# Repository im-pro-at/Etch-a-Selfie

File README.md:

# Etch-a-Selfie
ESP32_CAM meets Etch-A-Sketch => Etch-a-Selfie

## System Overview

## Software

The Software uses [GRBL](https://github.com/bdring/Grbl_Esp32) to controll the stepper motors.

A test implementation in JavaScript of the algorithms used is available [here](https://etch-a-selfie.im-pro.at/).

[Used Libraries](Sketch/ReadMe.md)

## BOM

[here](PCB/BOM.md)

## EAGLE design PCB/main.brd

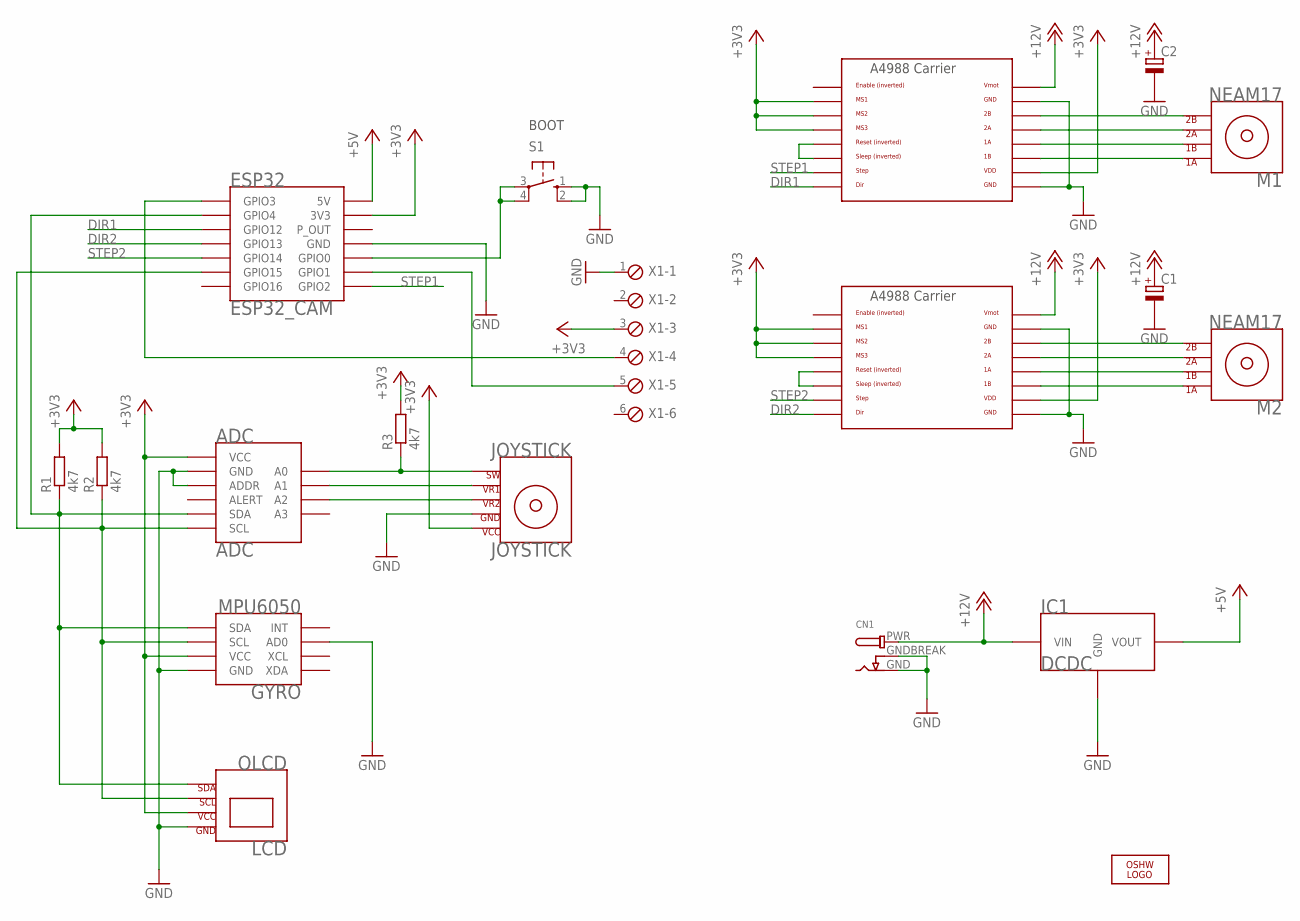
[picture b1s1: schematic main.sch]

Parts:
ADC: ADC
C1, C2: CPOL-EUE2.5-6; E2,5-6
CN1: DCBARRELPTH; DCJACK_2MM_PTH
ESP32: ESP32_CAM
GYRO: MPU6050
IC1: DCDC
IC2, IC3: A4988BREAKOUT
JOYSTICK: JOYSTICK
LCD: OLCD
LOGO1: OHW-LOGO_OSHW_LOGO_FILLX0350-NT; OHW-LOGO_OSHW_FILLX350_NOTEXT
M1, M2: NEAM17; NEMA17
R1, R2, R3: 4k7; 0207/10
S1: 10-XX; B3F-10XX
X1: MPT6; 6POL254

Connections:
+3V3: ADC.VCC, ESP32.3V3, GYRO.VCC, IC2.MS1, IC2.MS2, IC2.MS3, IC2.VDD, IC3.MS1, IC3.MS2, IC3.MS3, IC3.VDD, JOYSTICK.VCC, LCD.VCC, R1.2, R2.2, R3.2, X1.3
+5V: ESP32.5V, IC1.VOUT
+12V: C1.+, C2.+, CN1.PWR, IC1.VIN, IC2.VMOT, IC3.VMOT
DIR1: ESP32.GPIO12, IC2.DIR
DIR2: ESP32.GPIO13, IC3.DIR
GND: ADC.ADDR, ADC.GND, C1.-, C2.-, CN1.GND, CN1.GNDBREAK, ESP32.GND1 (GND), ESP32.GND2 (GND), ESP32.GND3 (GND), GYRO.AD0, GYRO.GND, IC1.GND1 (GND), IC1.GND2 (GND), IC2.GND, IC2.GND@0 (GND), IC3.GND, IC3.GND@0 (GND), JOYSTICK.GND, LCD.GND, S1.1 (S), S1.2 (S1), X1.1
unnamed: IC2.1B, M1.1A
unnamed: IC2.RST, IC2.SLP (SLEEP)
unnamed: IC2.2B, M1.2B
unnamed: IC2.2A, M1.2A
unnamed: IC2.1A, M1.1B
unnamed: IC3.RST, IC3.SLP (SLEEP)
unnamed: IC3.2B, M2.2B
unnamed: IC3.2A, M2.2A
unnamed: IC3.1A, M2.1B
unnamed: IC3.1B, M2.1A
unnamed: ESP32.GPIO1, X1.5
unnamed: ESP32.GPIO3, X1.4
unnamed: ESP32.GPIO0, S1.3, S1.4 (P1)
unnamed: ADC.A0, JOYSTICK.SW, R3.1
unnamed: ADC.A1, JOYSTICK.VR1
unnamed: ADC.A2, JOYSTICK.VR2
unnamed: ADC.SCL, ESP32.GPIO15, GYRO.SCL, LCD.SCL, R2.1
unnamed: ADC.SDA, ESP32.GPIO4, GYRO.SDA, LCD.SDA, R1.1
STEP1: ESP32.GPIO2, IC2.STEP
STEP2: ESP32.GPIO14, IC3.STEP

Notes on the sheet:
BOOT

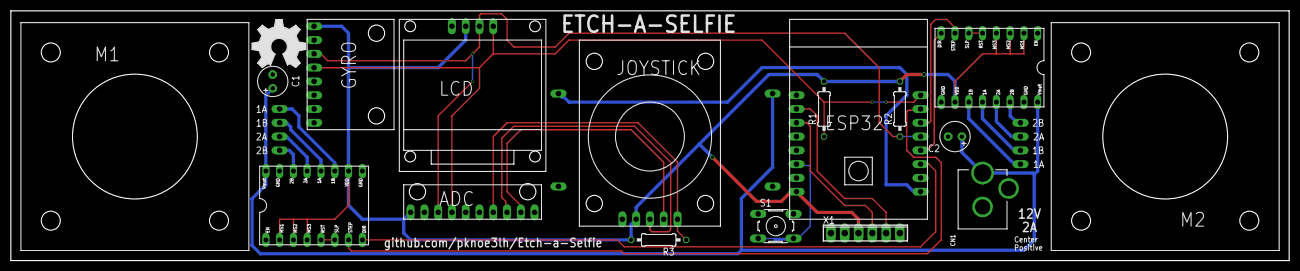
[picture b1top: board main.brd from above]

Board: 2 copper layers, 235.6 x 46.0 mm, 19 parts (1 on the bottom side), 26 nets.

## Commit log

2019-06-30 Add PCB
2019-06-30 Added GRBL source to be used to control the stepper motors
2019-06-30 cleaup
2019-07-01 moved grbl to the src folder
2019-07-01 Use grbl as a library ...
2019-07-01 Added OLED library
2019-07-04 PIN 16 is used by PSRAM ...
2019-07-04 We have an algorihm! Now test it on the ESP32 ...
2019-07-05 A* test implementation optimised for embedded use
2019-07-06 Finishing Algorithms ... looks good so far
2019-07-06 Some optimizations
2019-07-06 test
2019-07-06 Webcam is only working over https so Im hosting it on my server
2019-07-06 cleanup
2019-07-08 change debug port voltage to 3v3
2019-07-08 removed unchnaged libraries from src folder
2019-07-08 Added information about used libraries
2019-07-09 change N_AXIS is not a good idea ....
2019-07-09 moved read me
2019-07-09 fix typo ..
2019-07-13 fixed some problems with GRBL .. not perfect but should work now
2019-07-14 started to implement image converting algorithms in C ..
2019-07-15 again tried to fix grbl step pulse jitter
2019-07-17 More grbl tweaking ....
2019-07-17 C port of algorithm is working now
2019-07-17 Added missing ground connection on the jostick
2019-07-17 Jostick support added
2019-07-19 more grbl fun ...
2019-07-19 Start GUI design
2019-07-20 More GUI stuff
2019-07-21 better preview, add backlash compensation (not finished)
2019-07-23 lesson learned from prototype
2019-07-23 more GUI and optimisation, backlash comp is working now
2019-07-23 add job file for gerber generation
2019-07-24 more little updates
2019-07-25 Update Jostick handling
2019-07-25 This is it => V1
2019-07-28 add more informations
2019-07-30 Update LICENSE
2019-07-30 different versions => different PCBs

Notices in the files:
parts and their libraries:
microbuilder: This work is placed in the public domain, and may be freely used for commercial and non-commercial work with the following conditions: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
